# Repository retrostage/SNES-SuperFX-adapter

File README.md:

# SNES-SuperFX-adapter
(deprecated) A simple PCB adapter that allows the use of a M29F032, AM29F032/29F016 or MBM29F033 (or other pin compatible) flash memory to make a reproduction of a SNES game that uses the SuperFX (GSU-1 or GSU-2) or CX4 cartridge type. No manual wires or hot glue!

Included is the Gerber files (and a ".brd" file that works for OSH Park) which are needed for a PCB manufacturer to actually make the boards. The PDF instructions on how to assemble are included as well.

# NEW FOR 2025
The complete source for an upgraded design that uses modern and easily obtainable flash memory that you can find from places like Digikey or Mouser, like M29F160 and similar TSOP48 chips, has been added. This is the recommended design to use, as the old one is extremely outdated and uses flash memory that can only be found used, and often at expensive prices. This design is also easier for PCB fabs to produce. This design is intended for up to M29F160 (2MB) ROM sizes, but you can use M29F800 (1MB), or M29F400 (512KB) chips instead if your game is less than 2MB - or just double-up the ROM data with a hex editor and use the M29F160 for any game.

You can use EAGLE CAD or a compatible CAD program to open the source and view or change the design. Or just use the .brd file with your PCB manufacturer, most will accept that instead of gerber files.

These boards require castellation, a PCB manufacturing process that uses "half-vias" on the board edges, to ensure easy soldering to the donor cartridge. Check with your PCB manufacturer to make sure they support this feature (most do, at a slightly higher cost). Recommended PCB thickness is 1.0mm or even 0.8mm for best results.

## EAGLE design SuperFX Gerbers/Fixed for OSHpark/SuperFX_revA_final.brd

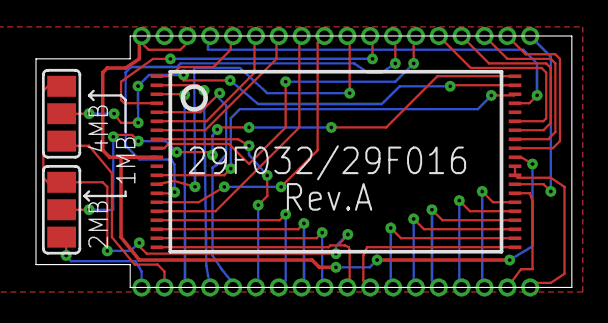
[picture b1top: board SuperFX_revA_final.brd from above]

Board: 2 copper layers, 29.8 x 14.0 mm, 3 parts (0 on the bottom side), 4 nets.

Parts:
20, 21: SJ_2
U$1: AM29F032B-E; 40-TSOP

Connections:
GND: 20.3, 21.3, U$1.29, U$1.30
unnamed: 21.2, U$1.39
unnamed: 20.2, U$1.40
VCC: U$1.10, U$1.12, U$1.31, U$1.38

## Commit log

2018-04-26 Uploaded files
2019-09-26 Create Fixed for OSHpark
2019-09-26 Update Fixed for OSHpark
2019-09-26 Fixed dimension outline issue that was causing shorting of all outside pins on the copper layer, affecting only OSHpark it seems.
2021-05-13 Added SuperFX .brd file
    Will help with anyone getting an error at OSH Park.
2025-09-21 Added new design
    Requires EAGLE or compatible CAD software - can use .brd file directly on most PCB manufacturer sites
2025-09-21 Update LICENSE
